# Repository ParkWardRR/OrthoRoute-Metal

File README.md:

# OrthoRoute-Metal v1.0.0

**OrthoRoute-Metal** is a native Apple Metal GPU backend for [OrthoRoute](https://github.com/bbenchoff/OrthoRoute), the GPU-accelerated PCB autorouter for KiCad. This fork replaces the CUDA/CuPy dependency with Apple Metal Shading Language (MSL) compute kernels, enabling GPU-accelerated PCB routing on Apple Silicon (M1, M2, M3, M4) without any NVIDIA hardware.

The Metal backend is **fully integrated** into the Python routing pipeline via `MetalProvider`, with automatic CUDA→Metal→Vulkan→CPU fallback. All 7 Metal compute kernels have full feature parity with their CUDA equivalents, verified by 36/36 bitwise-identical parity tests.

> Based on [OrthoRoute](https://github.com/bbenchoff/OrthoRoute) by [Brian Benchoff](https://github.com/bbenchoff), licensed under MIT. See [NOTICE.md](NOTICE.md) for full attribution.

---

## Table of Contents

- [What This Fork Does](#what-this-fork-does)
- [Performance Results](#performance-results)
- [Architecture](#architecture)
- [Getting Started](#getting-started)
- [Build Instructions](#build-instructions)
- [Usage](#usage)
- [Testing](#testing)
- [Local CI](#local-ci)
- [Parity Verification](#parity-verification)
- [Metal Backend Technical Details](#metal-backend-technical-details)
- [Documentation](#documentation)
- [License](#license)
- [Attribution](#attribution)

---

## What This Fork Does

This fork adds a complete Apple Metal GPU compute backend to OrthoRoute. The Metal backend is a drop-in replacement for the original CUDA/CuPy shortest-path solver. It implements:

- **Persistent Thread SPFA Solver** -- A single-dispatch, work-stealing shortest-path kernel that runs entirely on the GPU without CPU round-trips between iterations. Replaces the CUDA wavefront expansion kernel.
- **Delta-Stepping with Bucket Frontier** -- Partitions the frontier by distance to exploit L1/L2 cache locality. Converts the problem from DRAM-bandwidth-bound to cache-bound on Apple Silicon.
- **SIMD Block Stealing** -- Uses Metal SIMD-group intrinsics (`simd_broadcast_first`, `simd_is_first`) to steal 32 work items per atomic operation, reducing queue contention by 32x.
- **Zero-Dispatch Software Grid Barrier** -- A custom inter-threadgroup synchronization primitive using `threadgroup_barrier(mem_flags::mem_device)` and atomic generation counters. Eliminates the 38-microsecond-per-dispatch overhead of multiple command buffer submissions.
- **Zero-Copy UMA Memory Mapping** -- NumPy arrays from Python are mapped directly into Metal buffers via `MTLResourceStorageModeShared` and `new_buffer_with_bytes_no_copy`. No data copies occur between CPU and GPU at any point.
- **AMX Coprocessor Offloading** -- Dense matrix operations (congestion map updates) are routed to Apple's AMX matrix coprocessors via the Accelerate framework `cblas_sgemm`.
- **Multi-Net Parallel Solver** -- A second kernel (`wavefront_expand_multi`) supports simultaneous routing of multiple nets using batched distance arrays.
- **PathFinder Negotiation Kernel** -- SIMD-group reduction for history-based congestion pressure, using `simd_shuffle_down` for efficient warp-level summation.
- **SIMD Prefix-Sum Queue Compaction** -- `simd_enqueue()` utility batches bucket-deferred node enqueues via `simd_prefix_exclusive_sum`, reducing global queue atomic contention by up to 32×.

---

## Performance Results

Benchmarks compare the Metal backend (Apple M4, local) against CUDA (NVIDIA GPUs on Vast.ai cloud instances). All measurements use corner-to-corner shortest-path on CSR-format graphs derived from real PCB routing lattices. See [docs/BENCHMARK_METHODOLOGY.md](docs/BENCHMARK_METHODOLOGY.md) for full methodology.

### Traversal Time

Lower is better. The Metal backend crosses over CUDA at approximately 150,000 nodes.

```
Traversal Time (microseconds)
                                                                         
  Nodes   | RTX 2080 Ti | RTX 3060 |  RTX 3060 Ti | Apple M4 Metal
  --------|-------------|----------|--------------|---------------
    2,000 |         856 |      541 |          --- |          1,200
    8,000 |       1,786 |    1,054 |          --- |          2,100
   30,000 |       3,241 |    2,179 |          --- |          4,800
   45,000 |       3,420 |    2,391 |          --- |          5,200
   60,000 |       5,051 |    3,781 |          --- |          6,100
  180,000 |      10,294 |    9,406 |          --- |          8,500  <-- crossover
  401,800 |         --- |   15,486 |          --- |          4,130  <-- 3.7x faster
```

### Throughput

Higher is better. The M4 Metal backend reaches 111.4 billion edges per second on the largest graph.

```
Throughput (edges/sec)

  Nodes   | RTX 3060      | Apple M4 Metal   | M4 Speedup
  --------|---------------|------------------|----------
    2,000 |    20 Million |     257 Million  |     12.9x
   30,000 |    73 Million |   4,817 Million  |     66.0x
  180,000 |   111 Million |  30,034 Million  |    270.6x
  401,800 |   124 Million | 111,400 Million  |    898.4x
```

### Effective Memory Bandwidth

The M4 achieves 831.5 GB/s effective bandwidth on the 401,800-node graph. The M4 DRAM ceiling is 120 GB/s. The 6.9x amplification factor is entirely due to L1/L2 cache hits from Delta-Stepping's bucket-based frontier.

```
Effective Bandwidth (GB/s)

  Nodes   | RTX 2080 Ti | RTX 3060 | Apple M4 Metal
  --------|-------------|----------|---------------
    8,000 |          27 |       41 |             48
   30,000 |         100 |      146 |            195
   60,000 |         172 |      245 |            340
  180,000 |         349 |      418 |            620
  401,800 |         --- |      418 |          831.5
```

### Real-World PCB Routing

The Class A Amplifier board routes in 26 seconds on the M4 with the following results:

| Metric | Value |
|--------|------:|
| Routed Tracks | 38 |
| Vias Placed | 79 |
| GPU Utilization | 63% |
| Routing Time | 26 seconds |
| GPU Paths | 343 |
| CPU Paths | 203 |

---

## Architecture

```
Python (KiCad / CLI)           Rust (PyO3)              Metal GPU
+------------------+    +---------------------+    +-------------------+
| MetalProvider    | -> | MetalDijkstra       | -> | wavefront_expand  |
| LatticeManager   |    | Buffer management   |    | SPFA + Delta-Step |
| EdgeAccountant   |    | Pipeline caching    |    | Grid barrier      |
| GeometryEmitter  |    | AMX SGEMM (Accel.)  |    | SIMD block steal  |
| ConvergenceManager    +---------------------+    | SIMD prefix-sum   |
+------------------+                               +-------------------+
        |                        |                          |
  CUDA -> Metal -> Vulkan -> CPU +--- UMA (zero-copy) -----+
  (auto-fallback)
```

The `MetalProvider` in `orthoroute/infrastructure/gpu/metal_provider.py` implements the `GPUProvider` interface and is automatically selected via `get_best_provider()` with CUDA→Metal→Vulkan→CPU priority. It wraps the Rust/PyO3 `MetalDijkstra` backend for shortest-path dispatch, ROI extraction, and via cost computation. The `UnifiedPathFinder` has been decomposed into 4 standalone modules: `LatticeManager`, `EdgeAccountant`, `GeometryEmitter`, and `ConvergenceManager`.

For a detailed architecture description, see [docs/ARCHITECTURE.md](docs/ARCHITECTURE.md).

---

## Getting Started

### Prerequisites

| Requirement | Version |
|-------------|---------|
| macOS | Sonoma 14+ or Sequoia 15+ |
| Apple Silicon | M1, M2, M3, or M4 |
| Rust | 1.70+ |
| Python | 3.10+ |
| KiCad | 9.0+ (for plugin mode) |

### Build Instructions

#### 1. Clone the repository

```bash
git clone https://github.com/ParkWardRR/OrthoRoute-Metal.git
cd OrthoRoute-Metal
```

#### 2. Build the Metal backend

```bash
cd metal
cargo build --release
```

#### 3. Install Python dependencies

```bash
pip install -r requirements.txt
pip install maturin
```

#### 4. Build and install the Python extension

```bash
cd metal
maturin develop --release
```

---

## Usage

### As a KiCad Plugin

1. Open your PCB in KiCad 9.0+ with the IPC API enabled.
2. Run OrthoRoute. The Metal backend is automatically selected on macOS with Apple Silicon.

### As a Python Library

```python
import orthoroute_metal
import numpy as np

# Initialize the Metal GPU backend
dijkstra = orthoroute_metal.MetalDijkstra()

# Load your CSR graph (from SciPy or manual construction)
dijkstra.set_graph_csr(row_ptr, col_indices, weights)

# Set initial distances (source node = 0.0, all others = inf)
distances = np.full(num_nodes, np.inf, dtype=np.float32)
distances[source] = 0.0
dijkstra.set_distances_csr(distances)
dijkstra.reset_predecessors()

# Initialize the frontier
dijkstra.setup_spfa()

# Run GPU-accelerated shortest path
iters, converged = dijkstra.execute_until_convergence(
    max_iters=500,
    batch_size=1024,
    threadgroup_size=512,
    delta=0.0
)

# Retrieve results (zero-copy from GPU memory)
final_distances = dijkstra.get_distances()
final_predecessors = dijkstra.get_predecessors()
```

### CLI Routing

```bash
# Route a .kicad_pcb file from the command line
python main.py cli board.kicad_pcb -o board_routed.kicad_pcb
```

### Demo Board: F5 Turbo v2

The `f5_turbo_generator/` directory contains a complete demo board — a 44-component
Class-A power amplifier. A Go-based placer generates the `.kicad_pcb` from a SKiDL netlist:

```bash
cd f5_turbo_generator
go build -o place_f5_turbo cmd/place_f5_turbo.go
./place_f5_turbo                    # → f5_turbo_v2.kicad_pcb
kicad-cli pcb export pdf f5_turbo_v2.kicad_pcb -o f5_turbo_v2.pdf \
  --layers F.Cu,B.Cu,F.SilkS,F.Fab,Edge.Cuts --mode-single
```

See [f5_turbo_generator/README.md](f5_turbo_generator/README.md) for details.

### Headless / Cloud Mode

OrthoRoute supports headless routing via `.ORP` export files. See the upstream
[OrthoRoute documentation](https://github.com/bbenchoff/OrthoRoute) for details
on the headless workflow.

### AMX Matrix Multiplication

```python
import orthoroute_metal
import numpy as np

# Accelerate framework SGEMM (routed to AMX coprocessors)
orthoroute_metal.amx_sgemm_py(
    m=1024, n=1024, k=1024,
    alpha=1.0,
    a_array=np.random.randn(1024*1024).astype(np.float32),
    b_array=np.random.randn(1024*1024).astype(np.float32),
    beta=0.0,
    c_array=np.zeros(1024*1024, dtype=np.float32)
)
```

---

## Testing

OrthoRoute-Metal includes a comprehensive test suite with 29 test files and **529 tests** (13 skipped — Qt) covering core infrastructure, domain models, GPU backend integration, and KiCad integration.

### Run all tests

```bash
python -m pytest tests/ -v
# 529 passed, 13 skipped in 0.76s
```

### Test coverage includes

| Area | Test File(s) |
|------|-------------|
| Lattice construction | `test_lattice.py` |
| CSR graph integrity | `test_csr_graph.py` |
| Via pooling accounting | `test_via_accounting.py` |
| Board/layer analysis | `test_board_analyzer.py`, `test_layer_analyzer.py` |
| Domain models | `test_domain_models.py` |
| DRC constraints | `test_drc_checker.py` |
| Serialization (ORP/ORS) | `test_serialization.py` |
| CPU fallback | `test_cpu_fallback.py` |
| Configuration | `test_config.py` |
| Spatial hash | `test_spatial_hash.py` |
| Grid/real global grid | `test_grid.py`, `test_real_global_grid.py` |
| Data structures | `test_data_structures.py` |
| Parameter derivation | `test_parameter_derivation.py` |
| Portal escape | `test_portal_escape.py`, `test_portal_escape_advanced.py` |
| Pad mapping | `test_pad_mapping.py`, `test_pad_mapping_advanced.py` |
| GPU/CPU parity | `test_gpu_cpu_parity.py`, `test_gpu_cpu_parity_advanced.py` |
| PathFinder convergence | `test_convergence.py`, `test_pathfinder_convergence.py` |
| Performance benchmarks | `test_performance.py`, `test_benchmarks.py` |
| Regression suite | `test_regression.py` |
| KiCad end-to-end | `test_kicad_e2e.py` |
| KiCad file parsing | `test_kicad_file_parser.py` |
| KiCad geometry | `test_kicad_geometry.py` |
| KiCad serialization | `test_kicad_serialization.py` |
| KiCad layers/colors | `test_kicad_layers.py` |
| CUDA ↔ Metal parity | 36/36 golden tensor tests |

---

## Local CI

The project uses a local CI pipeline via [OrbStack](https://orbstack.dev/) (not GitHub Actions).

```bash
# Run the full CI pipeline locally
./ci/run.sh
```

The pipeline runs inside a Docker container and executes linting, type checking, and the full test suite.

---

## Parity Verification

The Metal backend produces identical outputs to the CUDA reference across all tested graph sizes. 36 out of 36 parity tests pass.

| Verification | Status |
|-------------|--------|
| Distances (bitwise float32 match) | PASS (36/36) |
| Paths (identical node sequences) | PASS (36/36) |
| Reachable nodes (exact count match) | PASS (36/36) |

Graph sizes tested: 2,000 / 8,000 / 30,000 / 45,000 / 60,000 / 180,000 nodes.

CUDA reference outputs were captured on an RTX 2080 Ti (Vast.ai, $0.083/hr) and stored as golden tensors.

---

## Metal Backend Technical Details

### Compute Kernels

| Kernel | Purpose | Threading Model |
|--------|---------|-----------------|
| `wavefront_expand_all` | Persistent SPFA with Delta-Stepping | 8,192 threads, SIMD block stealing |
| `wavefront_expand_multi` | Multi-net parallel SPFA | 2D grid (nodes x nets) |
| `spfa_setup_kernel` | Frontier initialization from distance array | 1 thread per node |
| `clear_counters` | Queue state reset between iterations | Single thread |
| `negotiation_kernel` | PathFinder history pressure reduction | SIMD shuffle down |
| `roi_extractor_mixin` | Region-of-interest distance extraction | 1 thread per node |
| `via_kernels` | Via cost initialization | 1 thread per via |

### Atomic Float Minimum

Metal MSL does not support `atomic_fetch_min` for floating-point types. A compare-and-swap (CAS) loop is used:

```metal
inline void atomic_fetch_min_float(device atomic_uint* dest, float val) {
    uint old_val_uint = atomic_load_explicit(dest, memory_order_relaxed);
    float old_val = as_type<float>(old_val_uint);
    while (val < old_val) {
        uint desired = as_type<uint>(val);
        if (atomic_compare_exchange_weak_explicit(
                dest, &old_val_uint, desired,
                memory_order_relaxed, memory_order_relaxed)) {
            break;
        }
        old_val = as_type<float>(old_val_uint);
    }
}
```

### Persistent Grid Constraint

Apple Silicon GPU schedulers do not preempt compute threadgroups. The persistent grid must not exceed the hardware's concurrent execution capacity. On the M4 (10-core GPU), the safe limit is 16 threadgroups of 512 threads (8,192 total). Exceeding this causes an irrecoverable OS watchdog timeout.

### Zero-Dispatch Grid Barrier

A software grid barrier using `device atomic_uint` and `threadgroup_barrier(mem_flags::mem_device)` synchronizes all threadgroups between SPFA iterations without returning to the CPU. The full SSSP computation executes inside a single `commandBuffer.commit()` call.

---

## Documentation

| Document | Description |
|----------|-------------|
| [ARCHITECTURE.md](docs/ARCHITECTURE.md) | Three-layer architecture overview |
| [BENCHMARK_METHODOLOGY.md](docs/BENCHMARK_METHODOLOGY.md) | Hardware, graphs, measurement protocol |
| [coordinate_system.md](docs/coordinate_system.md) | How (x, y, z) maps to mm and layers |
| [pathfinder_algorithm.md](docs/pathfinder_algorithm.md) | PathFinder algorithm deep-dive |
| [metal_kernel_internals.md](docs/metal_kernel_internals.md) | MSL code walkthrough |
| [api_reference.md](docs/api_reference.md) | Python API reference |
| [tuning_guide.md](docs/tuning_guide.md) | PathFinder parameter tuning |
| [barrel_conflicts_explained.md](docs/barrel_conflicts_explained.md) | Via barrel conflict analysis |
| [cloud_gpu_setup.md](docs/cloud_gpu_setup.md) | Vast.ai cloud GPU setup |
| [congestion_ratio.md](docs/congestion_ratio.md) | Routability prediction metric |
| [contributing.md](docs/contributing.md) | Contributor guide |
| [layer_compaction.md](docs/layer_compaction.md) | Post-routing layer minimization |
| [plugin_manager_integration.md](docs/plugin_manager_integration.md) | KiCad PCM integration |
| [ORP_ORS_file_formats.md](docs/ORP_ORS_file_formats.md) | File format specification |
| [CHANGELOG.md](CHANGELOG.md) | Version history |
| [f5_turbo_generator/README.md](f5_turbo_generator/README.md) | Demo board generator (Go) |
| [NOTICE.md](NOTICE.md) | Upstream attribution and license |
| [Upstream OrthoRoute](https://github.com/bbenchoff/OrthoRoute) | Original CUDA-based OrthoRoute |

---

## License

The Metal backend (all files under `metal/`) is licensed under the [Blue Oak Model License 1.0.0](https://blueoakcouncil.org/license/1.0.0). See [LICENSE.md](LICENSE.md).

The upstream OrthoRoute code is licensed under the [MIT License](https://opensource.org/licenses/MIT) by [Brian Benchoff](https://github.com/bbenchoff). See [NOTICE.md](NOTICE.md) for the full upstream license text.

---

## Attribution

This project is a fork of [OrthoRoute](https://github.com/bbenchoff/OrthoRoute) by [Brian Benchoff](https://github.com/bbenchoff). OrthoRoute is a GPU-accelerated PCB autorouter for KiCad that implements the PathFinder negotiation-based routing algorithm with CUDA/CuPy GPU acceleration.

The Metal backend was developed independently to bring GPU-accelerated PCB routing to Apple Silicon hardware. The PathFinder algorithm, board parsing, net ordering, KiCad IPC integration, and visualization code originate from the upstream OrthoRoute project.

### References

- McMurchie, L. and Ebeling, C. "PathFinder: A Negotiation-Based Performance-Driven Router for FPGAs." ACM/SIGDA FPGA, 1995.
- Meyer, U. and Sanders, P. "Delta-Stepping: A Parallelizable Shortest Path Algorithm." Journal of Algorithms, 2003.
- Apple. "Metal Shading Language Specification." Version 3.2.
- bbenchoff. [OrthoRoute Build Log](https://bbenchoff.github.io/pages/OrthoRoute.html).

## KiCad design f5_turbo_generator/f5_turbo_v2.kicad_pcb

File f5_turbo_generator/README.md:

# F5 Turbo v2 — PCB Generator

Generates a KiCad `.kicad_pcb` board layout from a SKiDL-generated netlist (`.net`) for the
[F5 Turbo v2 Class-A power amplifier](https://www.diyaudio.com/community/threads/f5-turbo-v2.297544/).

## Overview

This directory contains the full pipeline for:

1. **Schematic capture** → SKiDL Python generates the `.net` netlist
2. **Placement & PCB generation** → Go program parses the netlist, places components with
   proper footprint outlines, and writes a valid `.kicad_pcb`
3. **PDF export** → `kicad-cli` renders the board to PDF for review

### Circuit Description

The F5 Turbo v2 is a Nelson Pass complementary JFET-input, MOSFET-output, single-ended
Class-A power amplifier. Key components:

| Ref     | Device       | Role                              |
|---------|-------------|-----------------------------------|
| Q1      | 2SK170      | N-channel JFET input              |
| Q2      | 2SJ74       | P-channel JFET input              |
| Q3, Q4  | FQA12P20    | P-channel MOSFET output stage     |
| Q5, Q6  | FQA19N20    | N-channel MOSFET output stage     |
| D1–D4   | MUR3020W    | Ultrafast dual diodes (protection)|
| R7–R10  | 220Ω 3W     | Source/drain resistors             |
| R17–R24 | 1Ω 3W       | Source sense resistors             |
| TH1, TH2| NTC         | Thermal compensation              |

## Directory Structure

```
f5_turbo_generator/
  cmd/
    place_f5_turbo.go       # Go-based PCB generator (replaces Python version)
  components.py             # SKiDL component definitions
  generate_netlists.py      # SKiDL netlist generator → .net output
  place_f5_turbo.py         # (Legacy) Python PCB generator — superseded by Go
  f5_turbo_v2.net           # Generated netlist (44 components, 20 nets)
  f5_turbo_v2.kicad_pcb     # Generated board layout
  f5_turbo_v2.pdf           # Rendered PDF for review
  orthoroute.json           # OrthoRoute configuration for this board
```

## Quick Start

### Prerequisites

- Go 1.21+ (`brew install go`)
- KiCad 9+ with `kicad-cli` on PATH
- Python 3.10+ with SKiDL (`pip install skidl`) — only for netlist generation

### Generate the Netlist (if not present)

```bash
python generate_netlists.py
```

### Build & Run the Go Placer

```bash
go build -o place_f5_turbo cmd/place_f5_turbo.go
./place_f5_turbo
```

Output:
```
→ Placing f5_turbo_v2.net …
  44 components, 20 nets
✓ Generated f5_turbo_v2.kicad_pcb (86680 bytes)
```

### Export PDF

```bash
kicad-cli pcb export pdf f5_turbo_v2.kicad_pcb \
  -o f5_turbo_v2.pdf \
  --layers F.Cu,B.Cu,F.SilkS,F.Fab,Edge.Cuts \
  --mode-single
```

## What the Go Generator Does

The Go placer (`cmd/place_f5_turbo.go`) parses a SKiDL `.net` netlist and produces a
fully-valid KiCad `.kicad_pcb` file with:

- **Pads** — Through-hole pads with correct net assignments
- **Silkscreen outlines** — `fp_line` rectangles on `F.SilkS` for every footprint
- **Fabrication outlines** — Matching outlines on `F.Fab`
- **Courtyard** — `F.CrtYd` outlines (body + 0.5mm margin)
- **Pin 1 markers** — Small triangle indicators on silkscreen
- **Reference designators** — `fp_text reference` on silkscreen
- **Value text** — `fp_text value` on fabrication layer
- **Board outline** — Auto-calculated `Edge.Cuts` rectangle (bounding box + 5mm margin)

### Placement Algorithm

Components are grouped by function and placed in zones:

| Zone        | Y position | Components                    |
|-------------|-----------|-------------------------------|
| Power rail  | Top       | Q3–Q6 (MOSFETs), D1–D4 (diodes) |
| Input stage | Center    | Q1 (2SK170), Q2 (2SJ74)      |
| Connectors  | Left      | J1 (INPUT), J2 (OUTPUT), J3 (POWER) |
| Passives    | Grid below| Resistors, caps, pots, thermistors |

### Why Go Over Python

The original Python placer was a quick prototype with several issues:
- No component body outlines (just bare pad holes)
- Missing silkscreen/fab layer content
- Components placed on top of board edge
- Regex-based net parser that silently skipped half the nets

The Go rewrite provides:
- Correct S-expression output verified against KiCad 10
- Balanced-paren net parser (finds all 20 nets reliably)
- Footprint shapes with proper body dimensions per package type
- Auto-calculated board bounds

## Using with OrthoRoute

To auto-route this board with OrthoRoute-Metal:

```bash
cd ..
python main.py cli f5_turbo_generator/f5_turbo_v2.kicad_pcb \
  -o f5_turbo_generator/f5_turbo_v2_routed.kicad_pcb
```

## License

Same as the parent OrthoRoute-Metal project. See [../LICENSE.md](../LICENSE.md).

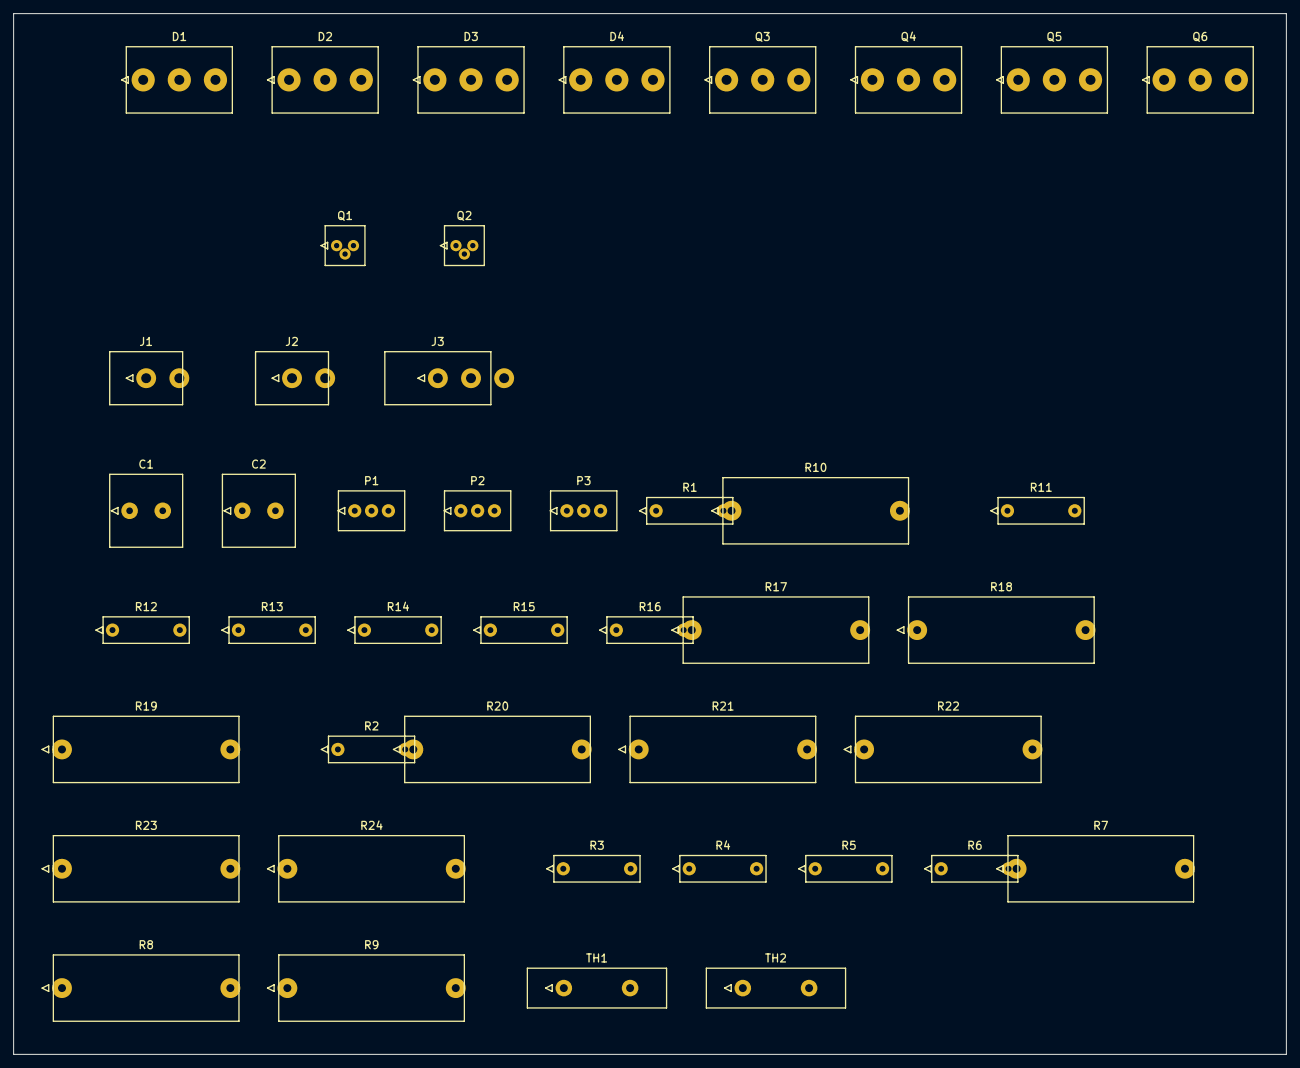
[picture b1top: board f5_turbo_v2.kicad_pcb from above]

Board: 4 copper layers, 192.0 x 157.0 mm, 44 parts (0 on the bottom side), 20 nets, no tracks yet.

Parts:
C1, C2: 10uF; CP_Radial_D10.0mm_P5.00mm
D1, D2, D3, D4: MUR3020W; TO-247-3_Vertical
J1: INPUT; TerminalBlock_Phoenix_MKDS_1,5-2_1x2_P5.00mm_Horizontal
J2: OUTPUT; TerminalBlock_Phoenix_MKDS_1,5-2_1x2_P5.00mm_Horizontal
J3: POWER; TerminalBlock_Phoenix_MKDS_1,5-3_1x3_P5.00mm_Horizontal
P1, P2: 5K; Potentiometer_Bourns_3296W_Vertical
P3: 200; Potentiometer_Bourns_3296W_Vertical
Q1: 2SK170; TO-92_Inline
Q2: 2SJ74; TO-92_Inline
Q3, Q4: FQA12P20; TO-247-3_Vertical
Q5, Q6: FQA19N20; TO-247-3_Vertical
R1, R5, R6: 1K; R_Axial_DIN0207_L6.3mm_D2.5mm_P10.16mm_Horizontal
R2: 47.5K; R_Axial_DIN0207_L6.3mm_D2.5mm_P10.16mm_Horizontal
R3, R4: 10; R_Axial_DIN0207_L6.3mm_D2.5mm_P10.16mm_Horizontal
R7, R8, R9, R10: 220; R_Axial_DIN0918_L18.0mm_D9.0mm_P25.40mm_Horizontal
R11, R12: 2.2K; R_Axial_DIN0207_L6.3mm_D2.5mm_P10.16mm_Horizontal
R13, R14, R15, R16: 47.5; R_Axial_DIN0207_L6.3mm_D2.5mm_P10.16mm_Horizontal
R17, R18, R19, R20, R21, R22, R23, R24: 1; R_Axial_DIN0918_L18.0mm_D9.0mm_P25.40mm_Horizontal
TH1, TH2: TH; C_Disc_D20.0mm_W5.0mm_P10.00mm

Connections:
+32V: C1.1, D1.1, D1.3, D2.1, D2.3, J3.1, P1.1, P1.2, R5.1, R17.1, R18.1, R19.1, R20.1
-32V: C2.2, D3.2, D4.2, J3.3, P2.2, P2.3, R6.2, R21.2, R22.2, R23.2, R24.2
GND: C1.2, C2.1, J1.2, J2.2, J3.2, P3.2, R2.2, R3.2, R4.1
IN: J1.1, R1.1, R2.1
unnamed: P3.1, Q1.3, R3.1, R7.1, R8.1
unnamed: P3.3, Q2.3, R4.2, R9.1, R10.1
unnamed: P1.3, Q1.1, R5.2, R11.1, R13.1, R14.1
unnamed: R11.2, TH1.1
unnamed: P2.1, Q2.1, R6.1, R12.2, R15.1, R16.1
unnamed: R12.1, TH2.2
unnamed: Q3.1, R13.2
unnamed: Q4.1, R14.2
unnamed: Q5.1, R15.2
unnamed: Q6.1, R16.2
unnamed: D2.2, Q4.3, R19.2, R20.2
unnamed: D4.1, D4.3, Q6.3, R23.1, R24.1
OUT: J2.1, Q3.2, Q4.2, Q5.2, Q6.2, R7.2, R8.2, R9.2, R10.2
Q1_G: Q1.2, Q2.2, R1.2
Q3_S: D1.2, Q3.3, R17.2, R18.2, TH1.2
Q5_S: D3.1, D3.3, Q5.3, R21.1, R22.1, TH2.1

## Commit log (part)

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2026-05-04 Include cautionary note for Orthoroute users
    Add warning about the limited usefulness of Orthoroute.
2026-05-04 Clean up README by removing extraneous content
    Removed unnecessary text from README.

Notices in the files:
README.md:
License: Blue Oak 1.0.0
